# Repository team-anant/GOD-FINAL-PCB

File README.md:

# GOD FINAL PCB
IDEAS
FAILSAFE POWER SUPPLY FOR EPS AND BEACON LIKE DIRECT PANEL TO EPS WITHOUT BUCK AND SHIT JUST PLAIN POWER 
GOALS
1. POWER SUPPLY
	A)PANEL IN 
		ARCHITECTURE AND CONFIG OF THE PANELS
		
2. POWER STORAGE
	BATTERY CONFIG: 2S2P
	BATTERY HEATER?
	BATTERY MONITORING?
	
3. POWER MONITORING
	PGEN MONITORING
	PNET UTIL MONITORING
4. POWER BUS WITH DEDICATED MONITORED LINES
	OBC
	PAYLOAD 1
	PAYLOAD 2
	PAYLOAD 3
	TTC 
	ADCS SENSOR PACKAGE
	ADCS CONTROL PACKAGE
	
5. OCPC DEDICATED LINES
	OBC
	PAYLOAD 1
	PAYLOAD 2
	PAYLOAD 3
	TTC 
	ADCS SENSOR PACKAGE
	ADCS CONTROL PACKAGE
6. POWER MONITORING INTERFACE
7. SENSOR INTERFACE
	BNO055
	GPS
	BEAGLE BONE BLACK
	
8. DATA STORAGE
9. DATA PACKETIZATION
10. DATA BEACON
11. WATCHDOG
	AUTO WATCHDOG
12. TEMPEARTURE MONITORING SYSTEM
	LTC2896

FAILOVER MODES:-
1. EPS OCPS

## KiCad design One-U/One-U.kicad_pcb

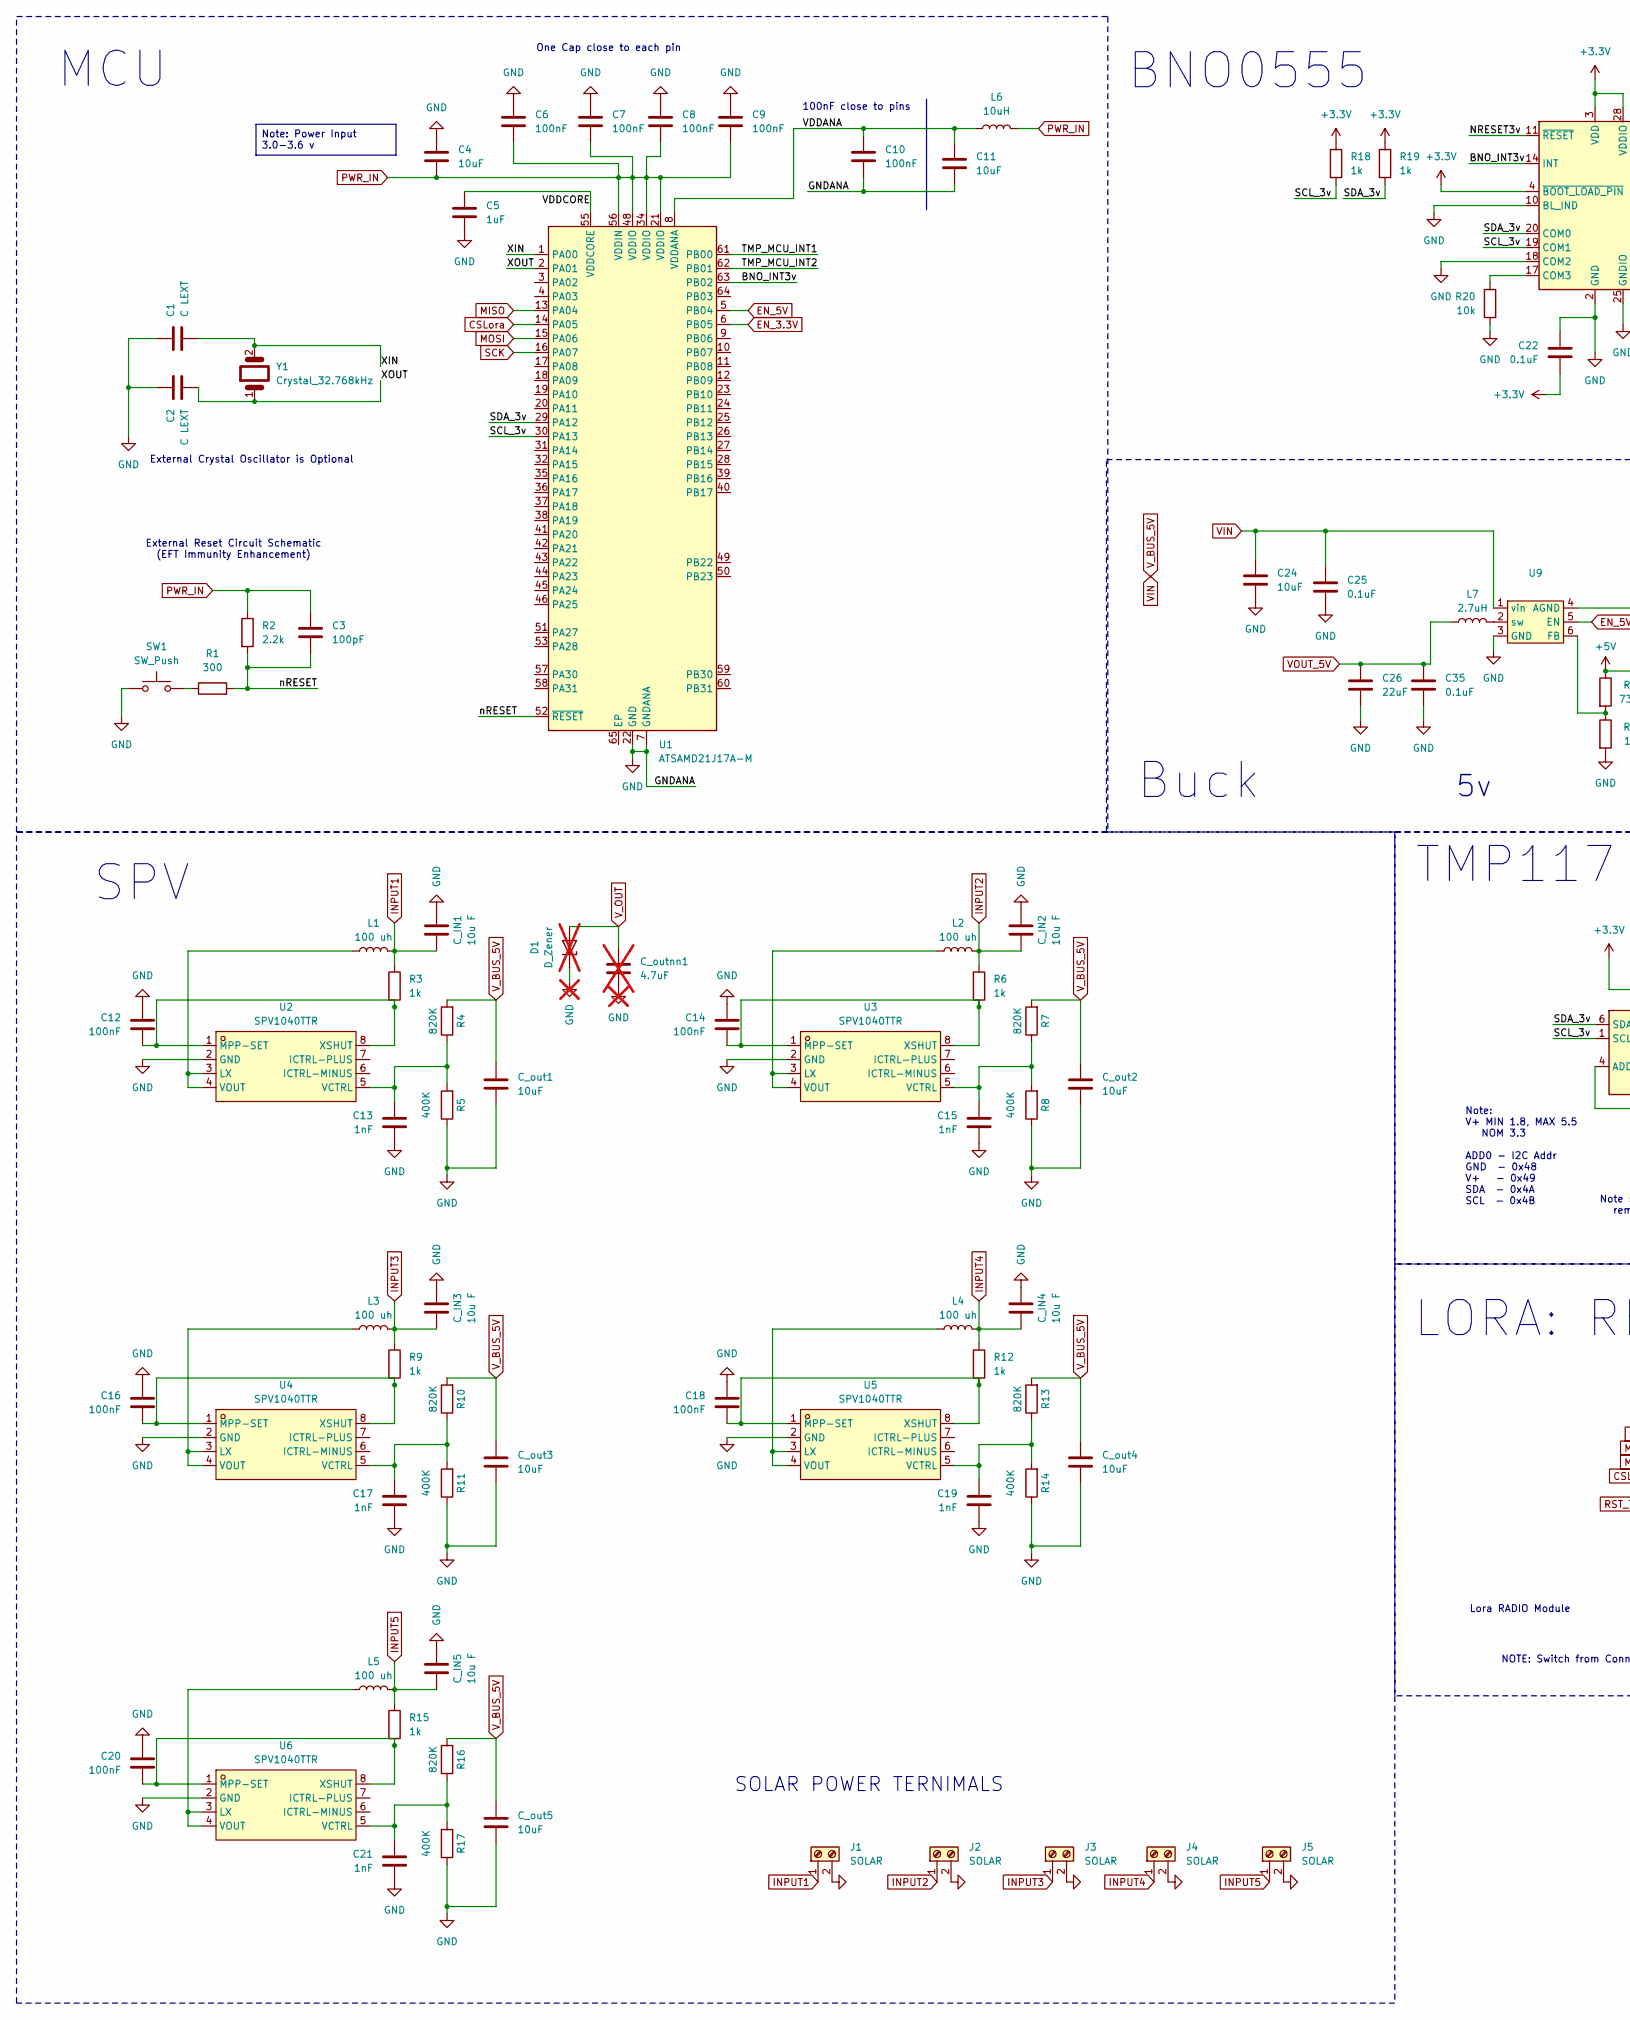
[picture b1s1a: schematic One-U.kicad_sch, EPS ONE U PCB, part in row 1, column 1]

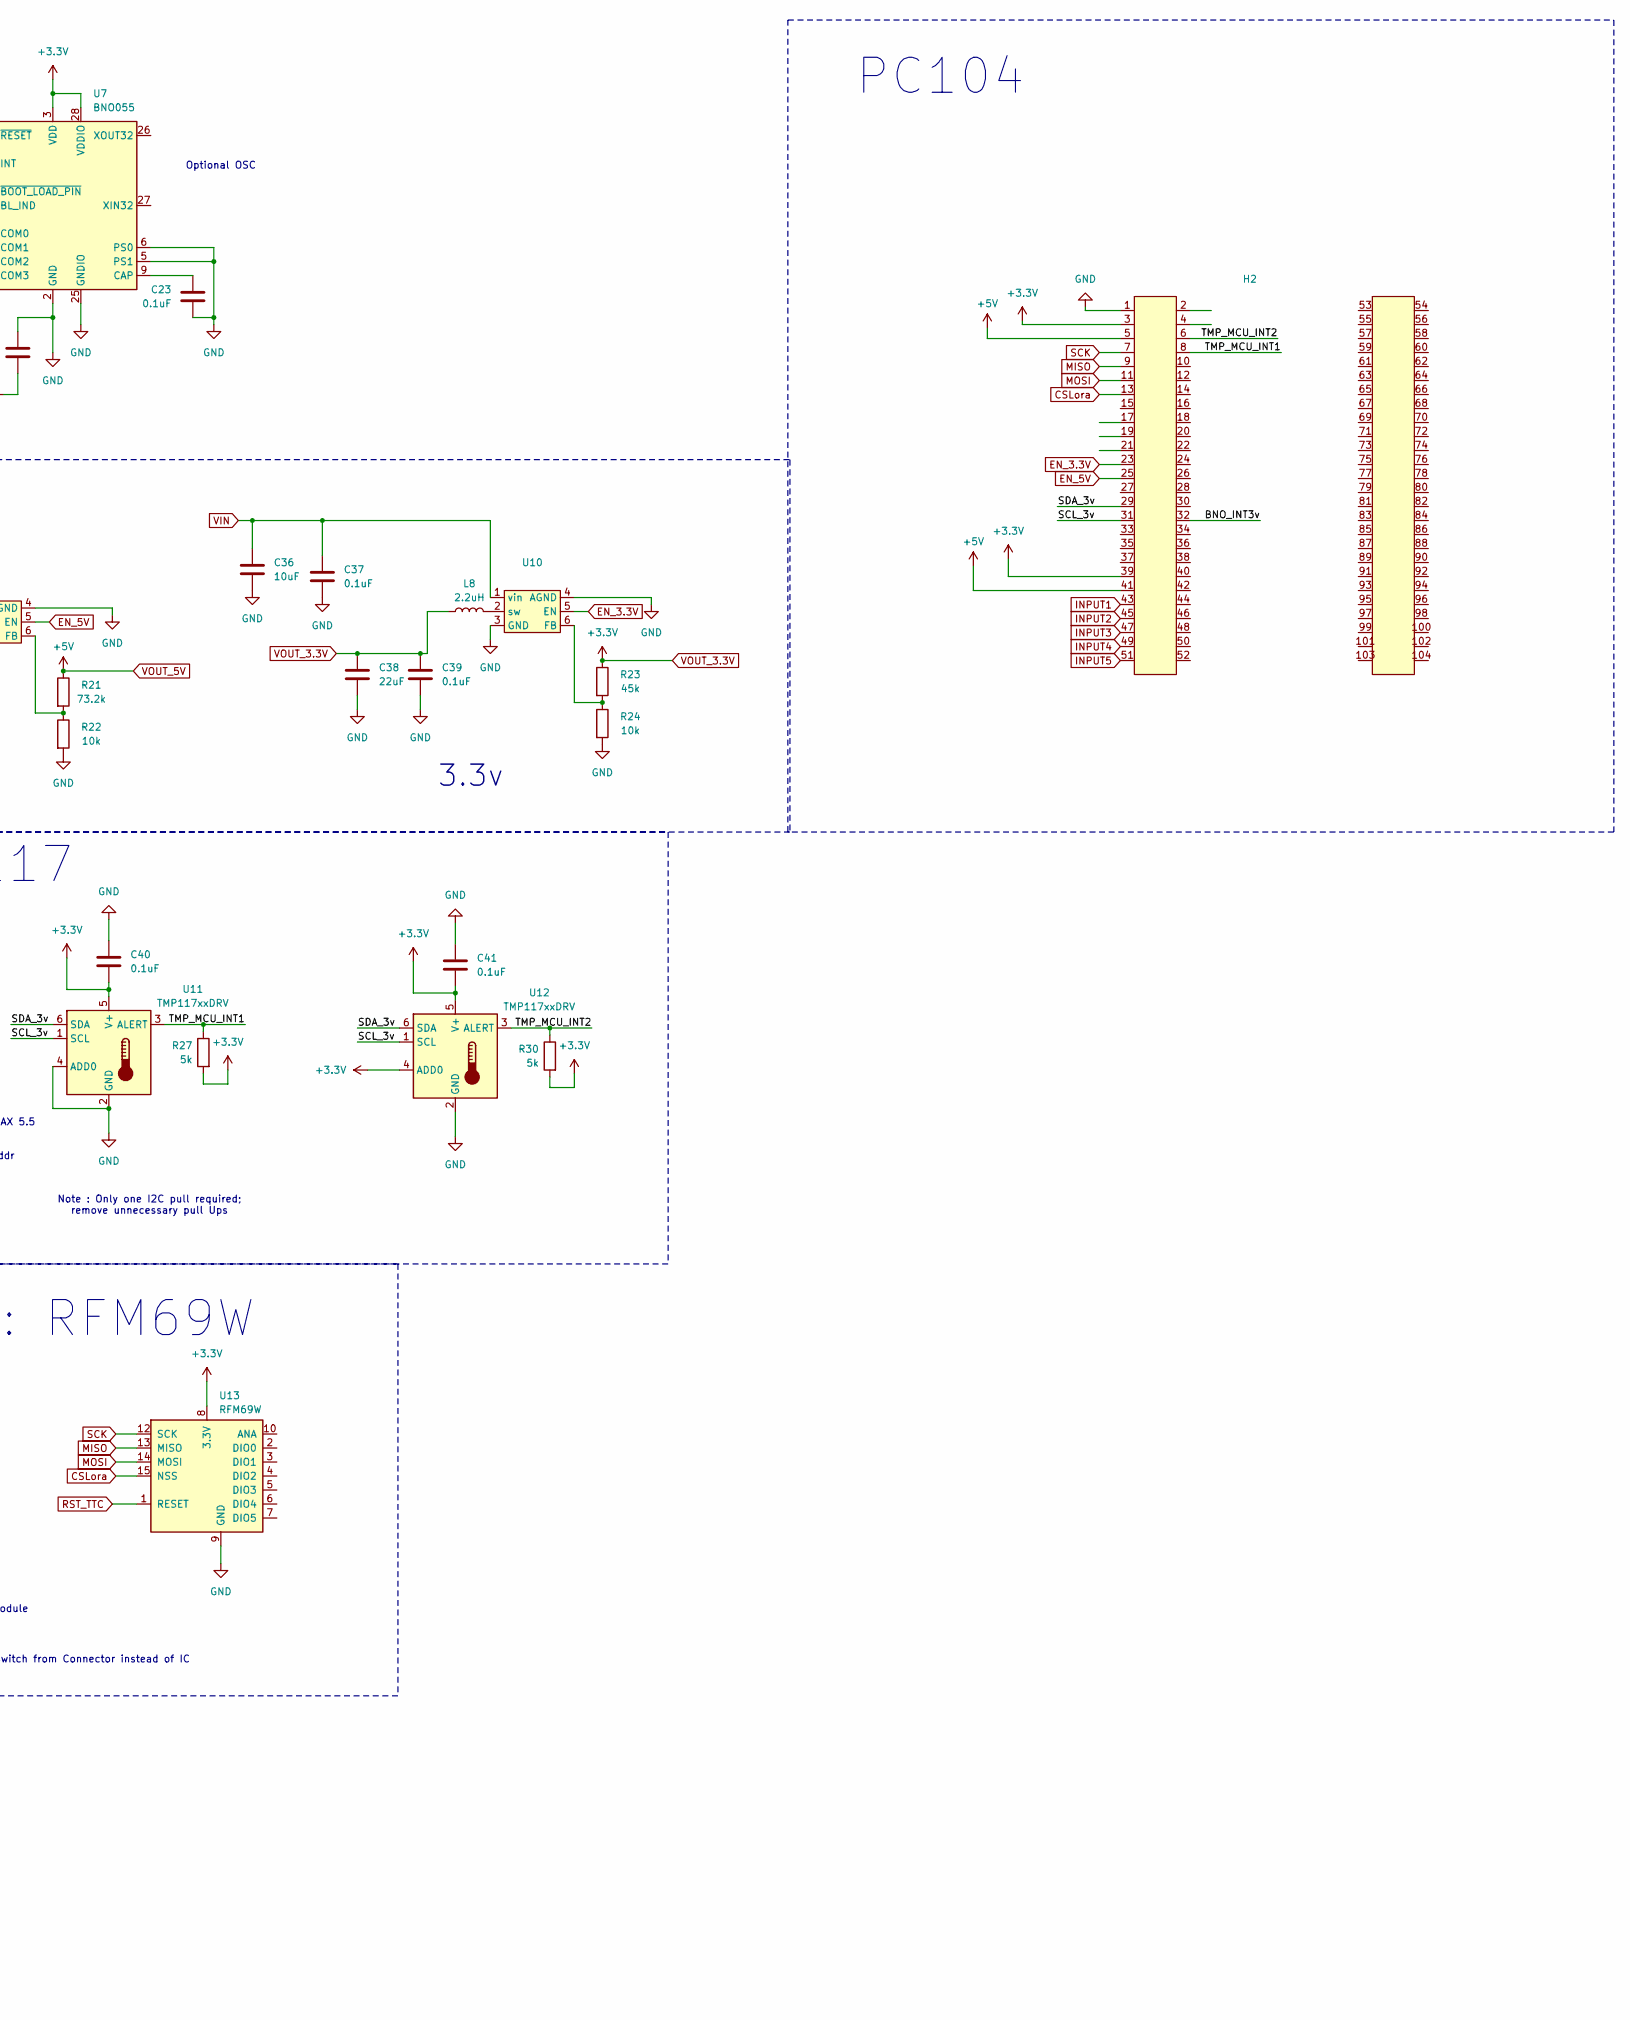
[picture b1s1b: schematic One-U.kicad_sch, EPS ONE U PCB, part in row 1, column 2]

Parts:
C1, C2: C LEXT; C_0603_1608Metric
C3: 100pF; C_0603_1608Metric
C4, C11, C24, C36: 10uF; C_0603_1608Metric
C5: 1uF; C_0603_1608Metric
C6, C7, C8, C9, C10, C12, C14, C16, C18, C20: 100nF; C_0603_1608Metric
C13, C15, C17, C19, C21: 1nF; C_0603_1608Metric
C22, C23, C25, C35, C37, C39, C40, C41: 0.1uF; C_0603_1608Metric
C26, C38: 22uF; C_0603_1608Metric
C_IN1, C_IN2, C_IN3, C_IN4, C_IN5: 10u F; C_0603_1608Metric
C_out1, C_out2, C_out3, C_out4, C_out5: 10uF; C_0603_1608Metric
C_outnn1: 4.7uF; C_0603_1608Metric; not fitted
D1: D_Zener; D_1210_3225Metric; not fitted
H2: PC104-Standard
J1, J2, J3, J4, J5: SOLAR; TerminalBlock_Phoenix_PT-1,5-2-5.0-H_1x02_P5.00mm_Horizontal
L1, L2, L3, L4, L5: 100 uh; L_Coilcraft_XAL6060-XXX
L6: 10uH; L_0805_2012Metric
L7: 2.7uH; L_Wuerth_MAPI-4020
L8: 2.2uH; L_Wuerth_MAPI-4020
R1: 300; R_0603_1608Metric
R2: 2.2k; R_0603_1608Metric
R3, R6, R9, R12, R15, R18, R19: 1k; R_0603_1608Metric
R4, R7, R10, R13, R16: 820K; R_0603_1608Metric
R5, R8, R11, R14, R17: 400K; R_0603_1608Metric
R20, R22, R24: 10k; R_0603_1608Metric
R21: 73.2k; R_0603_1608Metric
R23: 45k; R_0603_1608Metric
R27, R30: 5k; R_0603_1608Metric
SW1: SW_Push; SW_Push_1P1T_NO_E-Switch_TL3301NxxxxxG
U1: ATSAMD21J17A-M; QFN-64-1EP_9x9mm_P0.5mm_EP4.7x4.7mm
U2, U3, U4, U5, U6: SPV1040TTR; TSSOP-8_L4.4-W3.0-P0.65-LS6.4-BL; LCSC Part C221500
U7: BNO055; LGA-28_5.2x3.8mm_P0.5mm
U9, U10: SOT-23-6_Handsoldering
U11, U12: TMP117xxDRV; WSON-6-1EP_2x2mm_P0.65mm_EP1x1.6mm
U13: RFM69W; HOPERF_RFM69HW
Y1: Crystal_32.768kHz; Crystal_AT310_D3.0mm_L10.0mm_Vertical

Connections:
/BNO_INT3v: H2.32, U1.63 (PB02), U7.14 (INT)
/NRESET3v: U7.11 (~RESET)
/SCL_3v: H2.31, R18.2, U1.30 (PA13), U7.19 (COM1), U11.1 (SCL), U12.1 (SCL); also elsewhere on the board
/SDA_3v: H2.29, R19.2, U1.29 (PA12), U7.20 (COM0), U11.6 (SDA), U12.6 (SDA); also elsewhere on the board
/TMP_MCU_INT1: H2.8, R27.1, U1.61 (PB00), U11.3 (ALERT)
/TMP_MCU_INT2: H2.6, R30.1, U1.62 (PB01), U12.3 (ALERT)
/VDDANA: C10.1, C11.1, L6.1, U1.8 (VDDANA)
/VDDCORE: C5.1, U1.55 (VDDCORE)
/XIN: C1.2, U1.1 (PA00), Y1.2
/XOUT: C2.2, U1.2 (PA01), Y1.1
/nRESET: C3.2, R1.2, R2.2, U1.52 (~RESET)
CSLora: H2.13, U1.14 (PA05), U13.15 (NSS)
EN_3.3V: H2.23, U1.6 (PB05), U10.5 (EN)
EN_5V: H2.25, U1.5 (PB04), U9.5 (EN)
GND: C1.1, C2.1, C4.1, C5.2, C6.1, C7.1, C8.1, C9.1, C10.2, C11.2, C12.1, C13.2, C14.1, C15.2, C16.1, C17.2, C18.1, C19.2, C20.1, C21.2, C22.1, C23.2, C24.2, C25.2, C26.2, C35.2, C36.2, C37.2, C38.2, C39.2, C40.1, C41.1, C_IN1.2, C_IN2.2, C_IN3.2, C_IN4.2, C_IN5.2, C_out1.2, C_out2.2, C_out3.2, C_out4.2, C_out5.2, H2.1, J1.2, J2.2, J3.2, J4.2, J5.2, R5.1, R8.1, R11.1, R14.1, R17.1, R20.2, R22.2, R24.2, SW1.1, U1.7 (GNDANA), U1.22 (GND), U1.33 (GND), U1.47 (GND), U1.54 (GND), U2.2 (GND), U3.2 (GND), U4.2 (GND), U5.2 (GND), U6.2 (GND), U7.2 (GND), U7.5 (PS1), U7.6 (PS0), U7.10 (BL_IND), U7.18 (COM2), U7.25 (GNDIO), U9.3 (GND), U9.4 (AGND), U10.3 (GND), U10.4 (AGND), U11.2 (GND), U11.4 (ADD0), U12.2 (GND), U13.9 (GND), U13.11 (GND); also elsewhere on the board
INPUT1: C_IN1.1, H2.43, J1.1, L1.2, R3.1
INPUT2: C_IN2.1, H2.45, J2.1, L2.2, R6.1
INPUT3: C_IN3.1, H2.47, J3.1, L3.2, R9.1
INPUT4: C_IN4.1, H2.49, J4.1, L4.2, R12.1
INPUT5: C_IN5.1, H2.51, J5.1, L5.2, R15.1
MISO: H2.9, U1.13 (PA04), U13.13 (MISO)
MOSI: H2.11, U1.15 (PA06), U13.14 (MOSI)
unnamed: C_outnn1.2, D1.2 (A)
unnamed 26: U13.10 (ANA); also elsewhere on the board
unnamed: R1.1, SW1.2
unnamed: L1.1, U2.3 (LX), U2.4 (VOUT)
unnamed: C12.2, R3.2, U2.1 (MPP-SET), U2.8 (XSHUT)
unnamed: C13.1, R4.1, R5.2, U2.5 (VCTRL)
unnamed: L2.1, U3.3 (LX), U3.4 (VOUT)
unnamed: C14.2, R6.2, U3.1 (MPP-SET), U3.8 (XSHUT)
unnamed: C15.1, R7.1, R8.2, U3.5 (VCTRL)
unnamed: L3.1, U4.3 (LX), U4.4 (VOUT)
unnamed: C16.2, R9.2, U4.1 (MPP-SET), U4.8 (XSHUT)
unnamed: C17.1, R10.1, R11.2, U4.5 (VCTRL)
unnamed: L4.1, U5.3 (LX), U5.4 (VOUT)
unnamed: C18.2, R12.2, U5.1 (MPP-SET), U5.8 (XSHUT)
unnamed: C19.1, R13.1, R14.2, U5.5 (VCTRL)
unnamed: L5.1, U6.3 (LX), U6.4 (VOUT)
unnamed: C20.2, R15.2, U6.1 (MPP-SET), U6.8 (XSHUT)
unnamed: C21.1, R16.1, R17.2, U6.5 (VCTRL)
unnamed: C23.1, U7.9 (CAP)
unnamed: R20.1, U7.17 (COM3)
unnamed: R21.2, R22.1, U9.6 (FB)
unnamed: L7.1, U9.2 (sw)
unnamed: R23.2, R24.1, U10.6 (FB)
unnamed: L8.1, U10.2 (sw)
PWR_IN: C3.1, C4.2, C6.2, C7.2, C8.2, C9.2, L6.2, R2.1, U1.21 (VDDIO), U1.34 (VDDIO), U1.48 (VDDIO), U1.56 (VDDIN)
RST_TTC: U1.10 (PB07), U13.1 (RESET)
SCK: H2.7, U1.16 (PA07), U13.12 (SCK)
STAT: U1.9 (PB06); also elsewhere on the board
VIN: C24.1, C25.1, C36.1, C37.1, C_out1.1, C_out2.1, C_out3.1, C_out4.1, C_out5.1, R4.2, R7.2, R10.2, R13.2, R16.2, U9.1 (vin), U10.1 (vin); also elsewhere on the board
VOUT_3.3V: C22.2, C38.1, C39.1, C40.2, C41.2, H2.3, H2.39, L8.2, R18.1, R19.1, R23.1, R27.2, R30.2, U7.3 (VDD), U7.4 (~BOOT_LOAD_PIN), U7.28 (VDDIO), U11.5 (V+), U12.4 (ADD0), U12.5 (V+), U13.8 (3.3V)
VOUT_5V: C26.1, C35.1, H2.5, H2.41, L7.2, R21.1

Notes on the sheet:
Optional OSC
100nF close to pins
Buck
Note: V+ MIN 1.8, MAX 5.5 NOM 3.3 ADD0 - I2C Addr GND - 0x48 V+ - 0x49 SDA - 0x4A SCL - 0x4B
One Cap close to each pin
MCU
External Reset Circuit Schematic (EFT Immunity Enhancement)
Lora RADIO Module
SPV
PC104
NOTE: Switch from Connector instead of IC
SOLAR POWER TERNIMALS
TMP117
Note : Only one I2C pull required; remove unnecessary pull Ups
LORA: RFM69W
3.3v
External Crystal Oscillator is Optional
BNO0555
Note: Power Input 3.0-3.6 v

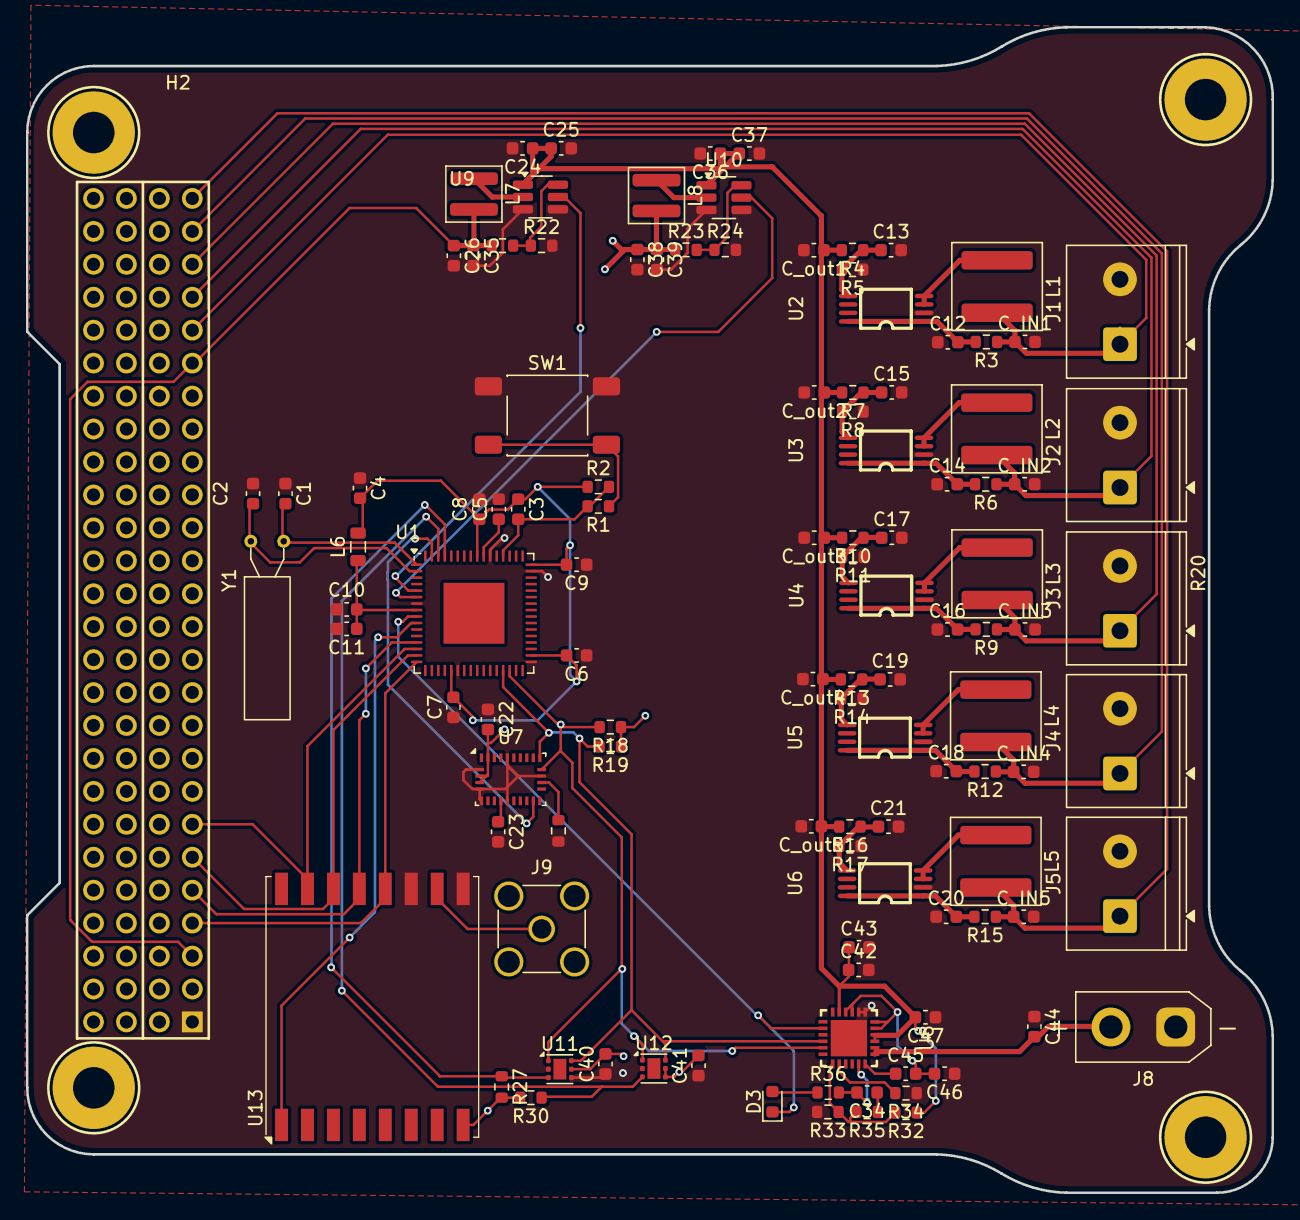
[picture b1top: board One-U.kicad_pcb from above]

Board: 4 copper layers, 96.0 x 89.9 mm, 113 parts (0 on the bottom side), 59 nets.

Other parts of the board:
C34: 4.7uF; C_0603_1608Metric
C42, C43: 22uF; C_0603_1608Metric
C44, C46: 10uF; C_0603_1608Metric
C45: 47uF; C_0603_1608Metric
C47: 1uF; C_0603_1608Metric
D3: LED; LED_0603_1608Metric
J8: Conn_01x02_Socket; AMASS_XT30UPB-F_1x02_P5.0mm_Vertical
J9: Conn_Coaxial_Small; SMA_Amphenol_132134-11_Vertical
R32: 5.23k; R_0603_1608Metric
R33: 30.1k; R_0603_1608Metric
R34: 3.16k; R_0603_1608Metric
R35, R36: 10k; R_0603_1608Metric
U8: BQ25883RGER; VFQFPN-24_L4.0-W4.0-P0.50-BL-EP2.8

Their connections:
/SCL_3v: U8.5 (SCL); also elsewhere on the board
/SDA_3v: U8.4 (SDA); also elsewhere on the board
GND: C42.2, C43.2, C44.1, C46.1, C47.1, J8.1, R33.2, R34.1, U8.19 (GND), U8.20 (GND), U8.25 (EP); also elsewhere on the board
unnamed: C34.1, R35.1
unnamed: C45.2, C46.2, U8.17 (SW), U8.18 (SW), U8.21 (PMID), U8.22 (PMID)
unnamed: D3.2 (A), R36.1
unnamed 26: J9.1 (In); also elsewhere on the board
unnamed: C45.1, U8.12 (BTST)
unnamed: R34.2, U8.8 (ILIM)
unnamed: C34.2, R36.2, U8.11 (REGN)
STAT: D3.1 (K), U8.2 (STAT); also elsewhere on the board
THM: R32.2, R33.1, R35.2, U8.7 (TS)
VIN: C42.1, C43.1, C47.2, R32.1, U8.15 (SYS), U8.16 (SYS), U8.23 (VBUS); also elsewhere on the board
V_BAT: C44.2, J8.2, U8.13 (BAT), U8.14 (BAT)

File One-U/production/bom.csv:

Designator,Footprint,Quantity,Value,LCSC Part #
"C1, C2",0603,2,C LEXT,
"C10, C12, C14, C16, C18, C20, C6, C7, C8, C9",0603,10,100nF,
"C11, C24, C36, C4, C44, C46, C_OUT1, C_OUT2, C_OUT3, C_OUT4, C_OUT5",0603,11,10uF,
"C13, C15, C17, C19, C21",0603,5,1nF,
"C22, C23, C25, C35, C37, C39, C40, C41",0603,8,0.1uF,
"C26, C38, C42, C43",0603,4,22uF,
C3,0603,1,100pF,
C34,0603,1,4.7uF,
C45,0603,1,47uF,
"C47, C5",0603,2,1uF,
"C_IN1, C_IN2, C_IN3, C_IN4, C_IN5",0603,5,10u F,
D3,0603,1,LED,
H2,PC104-Standard,1,~,
"J1, J2, J3, J4, J5","TerminalBlock_Phoenix_PT-1,5-2-5.0-H_1x02_P5.00mm_Horizontal",5,SOLAR,
J8,AMASS_XT30UPB-F_1x02_P5.0mm_Vertical,1,Conn_01x02_Socket,
J9,SMA_Amphenol_132134-11_Vertical,1,Conn_Coaxial_Small,
"L1, L2, L3, L4, L5",L_Coilcraft_XAL6060-XXX,5,100 uh,
L6,0805,1,10uH,
L7,L_Wuerth_MAPI-4020,1,2.7uH,
L8,L_Wuerth_MAPI-4020,1,2.2uH,
R1,0603,1,300,
"R10, R13, R16, R4, R7",0603,5,820K,
"R11, R14, R17, R5, R8",0603,5,400K,
"R12, R15, R18, R19, R3, R6, R9",0603,7,1k,
R2,0603,1,2.2k,
"R20, R22, R24, R35, R36",0603,5,10k,
R21,0603,1,73.2k,
R23,0603,1,45k,
"R27, R30",0603,2,5k,
R32,0603,1,5.23k,
R33,0603,1,30.1k,
R34,0603,1,3.16k,
SW1,SW_Push_1P1T_NO_E-Switch_TL3301NxxxxxG,1,SW_Push,
U1,QFN-64-1EP_9x9mm_P0.5mm_EP4.7x4.7mm,1,ATSAMD21J17A-M,
"U10, U9",SOT-23-6_Handsoldering,2,~,
"U11, U12",WSON-6-1EP_2x2mm_P0.65mm_EP1x1.6mm,2,TMP117xxDRV,
U13,HOPERF_RFM69HW,1,RFM69W,
"U2, U3, U4, U5, U6",TSSOP-8_L4.4-W3.0-P0.65-LS6.4-BL,5,SPV1040TTR,C221500
U7,LGA-28_5.2x3.8mm_P0.5mm,1,BNO055,
U8,VFQFPN-24_L4.0-W4.0-P0.50-BL-EP2.8,1,BQ25883RGER,C544362
Y1,Crystal_AT310_D3.0mm_L10.0mm_Horizontal,1,Crystal_32.768kHz,

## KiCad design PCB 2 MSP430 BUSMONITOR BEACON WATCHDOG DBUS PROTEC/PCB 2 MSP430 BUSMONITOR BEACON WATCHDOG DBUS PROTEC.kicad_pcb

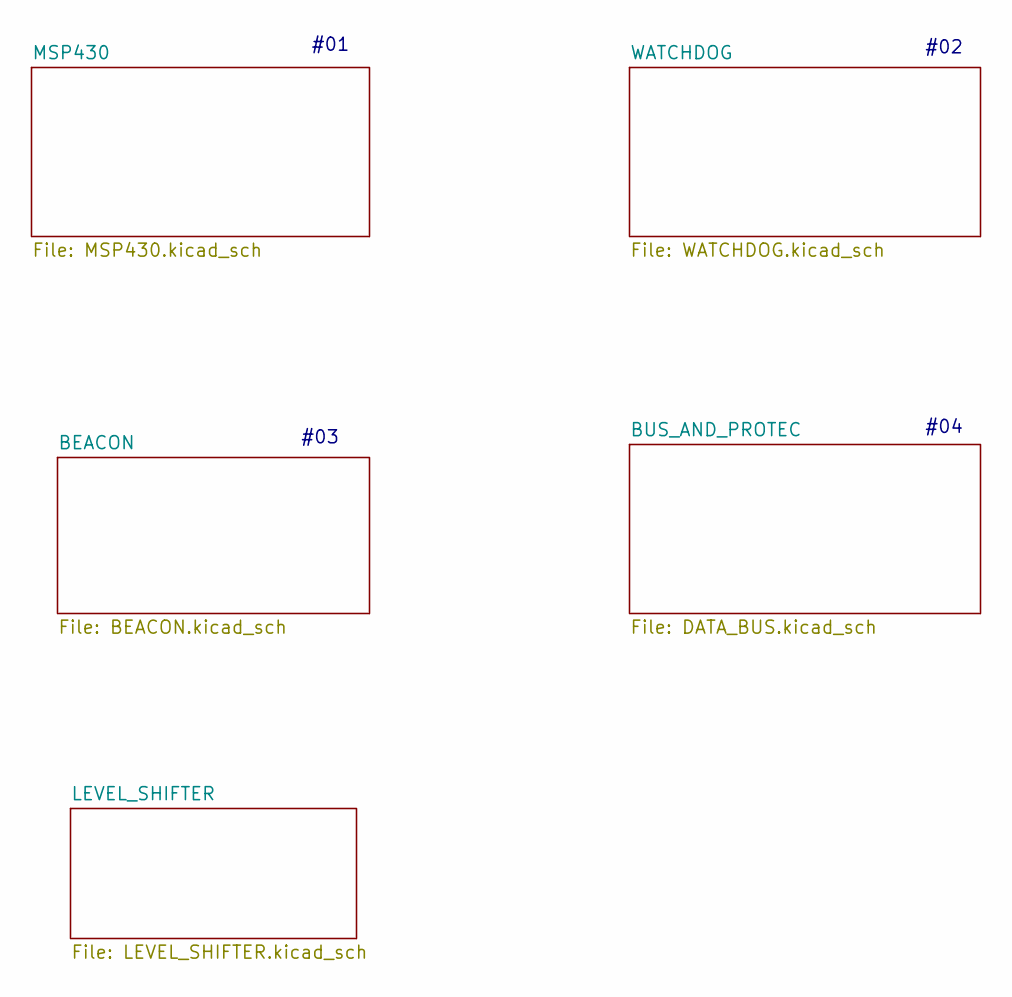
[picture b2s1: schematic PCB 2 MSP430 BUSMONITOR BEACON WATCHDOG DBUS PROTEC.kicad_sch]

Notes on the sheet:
#03
#01
#04
#02

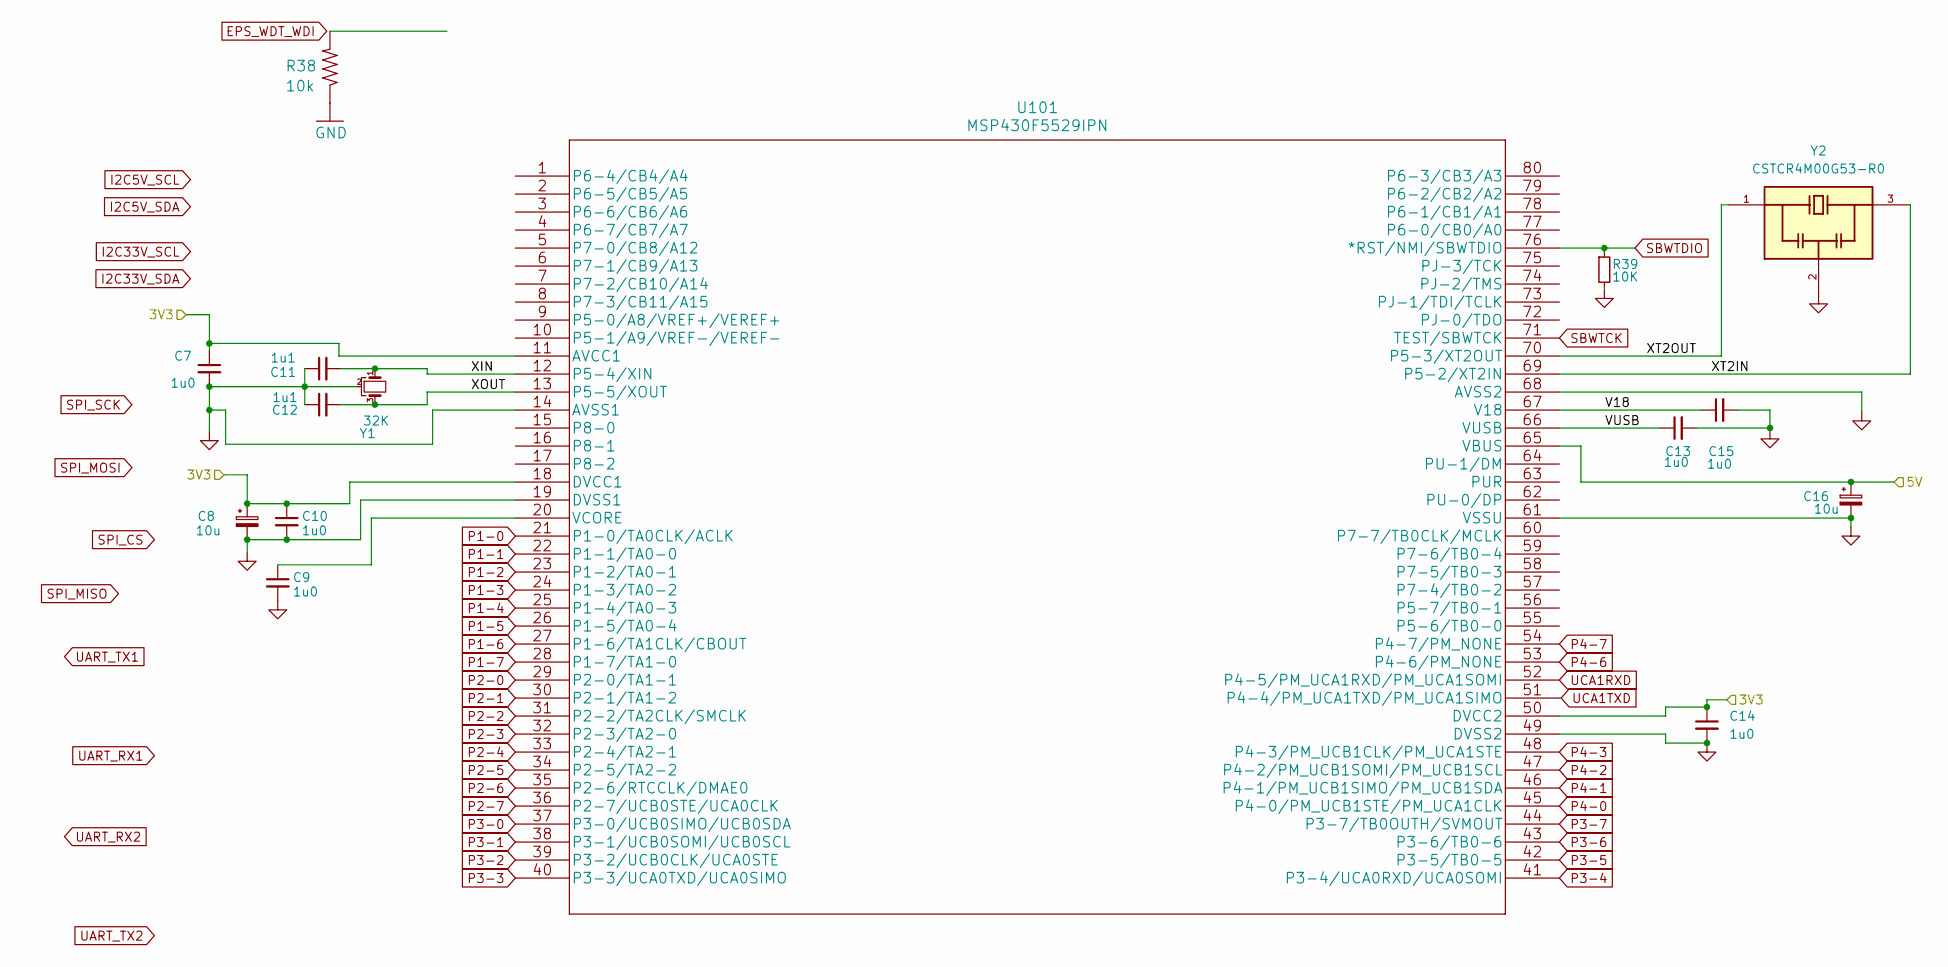
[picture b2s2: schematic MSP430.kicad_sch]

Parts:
C7, C9, C10, C14: 1u0; C_0603_1608Metric
C8: 10u; CP_Elec_3x5.3
C11, C12: 1u1; C_0603_1608Metric
C13, C15: 1u0; C_0402_1005Metric_Pad0.74x0.62mm_HandSolder
C16: 10u; CP_Elec_4x3.9
R38: 10k; R_0603_1608Metric
R39: 10K; R_0603_1608Metric
U101: MSP430F5529IPN
Y1: 32K; Crystal_AT310_D3.0mm_L10.0mm_Horizontal_1EP_style1
Y2: CSTCR4M00G53-R0; OSC_CSTCR4M00G53-R0; PARTREV JGC42-8797

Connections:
/MSP430/3V3: C7.1, C8.1, C10.1, C14.1, U101.11 (AVCC1), U101.18 (DVCC1), U101.50 (DVCC2)
/MSP430/5V: C16.1, U101.65 (VBUS)
/MSP430/V18: C15.1, U101.67 (V18)
/MSP430/VUSB: C13.1, U101.66 (VUSB)
/MSP430/XIN: C11.2, U101.12 (P5-4/XIN), Y1.1
/MSP430/XOUT: C12.2, U101.13 (P5-5/XOUT), Y1.3
GND: C7.2, C8.2, C9.2, C10.2, C11.1, C12.1, C13.2, C14.2, C15.2, C16.2, R38.1, R39.2, U101.14 (AVSS1), U101.19 (DVSS1), U101.49 (DVSS2), U101.61 (VSSU), U101.68 (AVSS2), Y1.2, Y2.2; also elsewhere on the board
unnamed: U101.69 (P5-2/XT2IN), Y2.3
unnamed: U101.70 (P5-3/XT2OUT), Y2.1
unnamed: C9.1, U101.20 (VCORE)
SBWTDIO: R39.1, U101.76 (*RST/NMI/SBWTDIO)

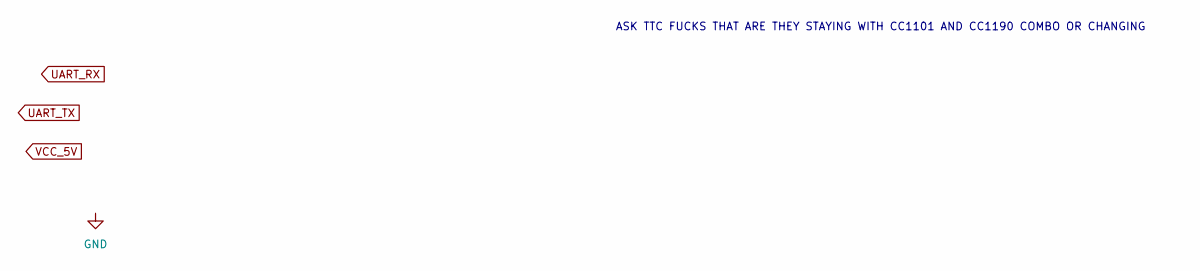
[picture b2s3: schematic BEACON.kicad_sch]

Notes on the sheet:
ASK TTC FUCKS THAT ARE THEY STAYING WITH CC1101 AND CC1190 COMBO OR CHANGING

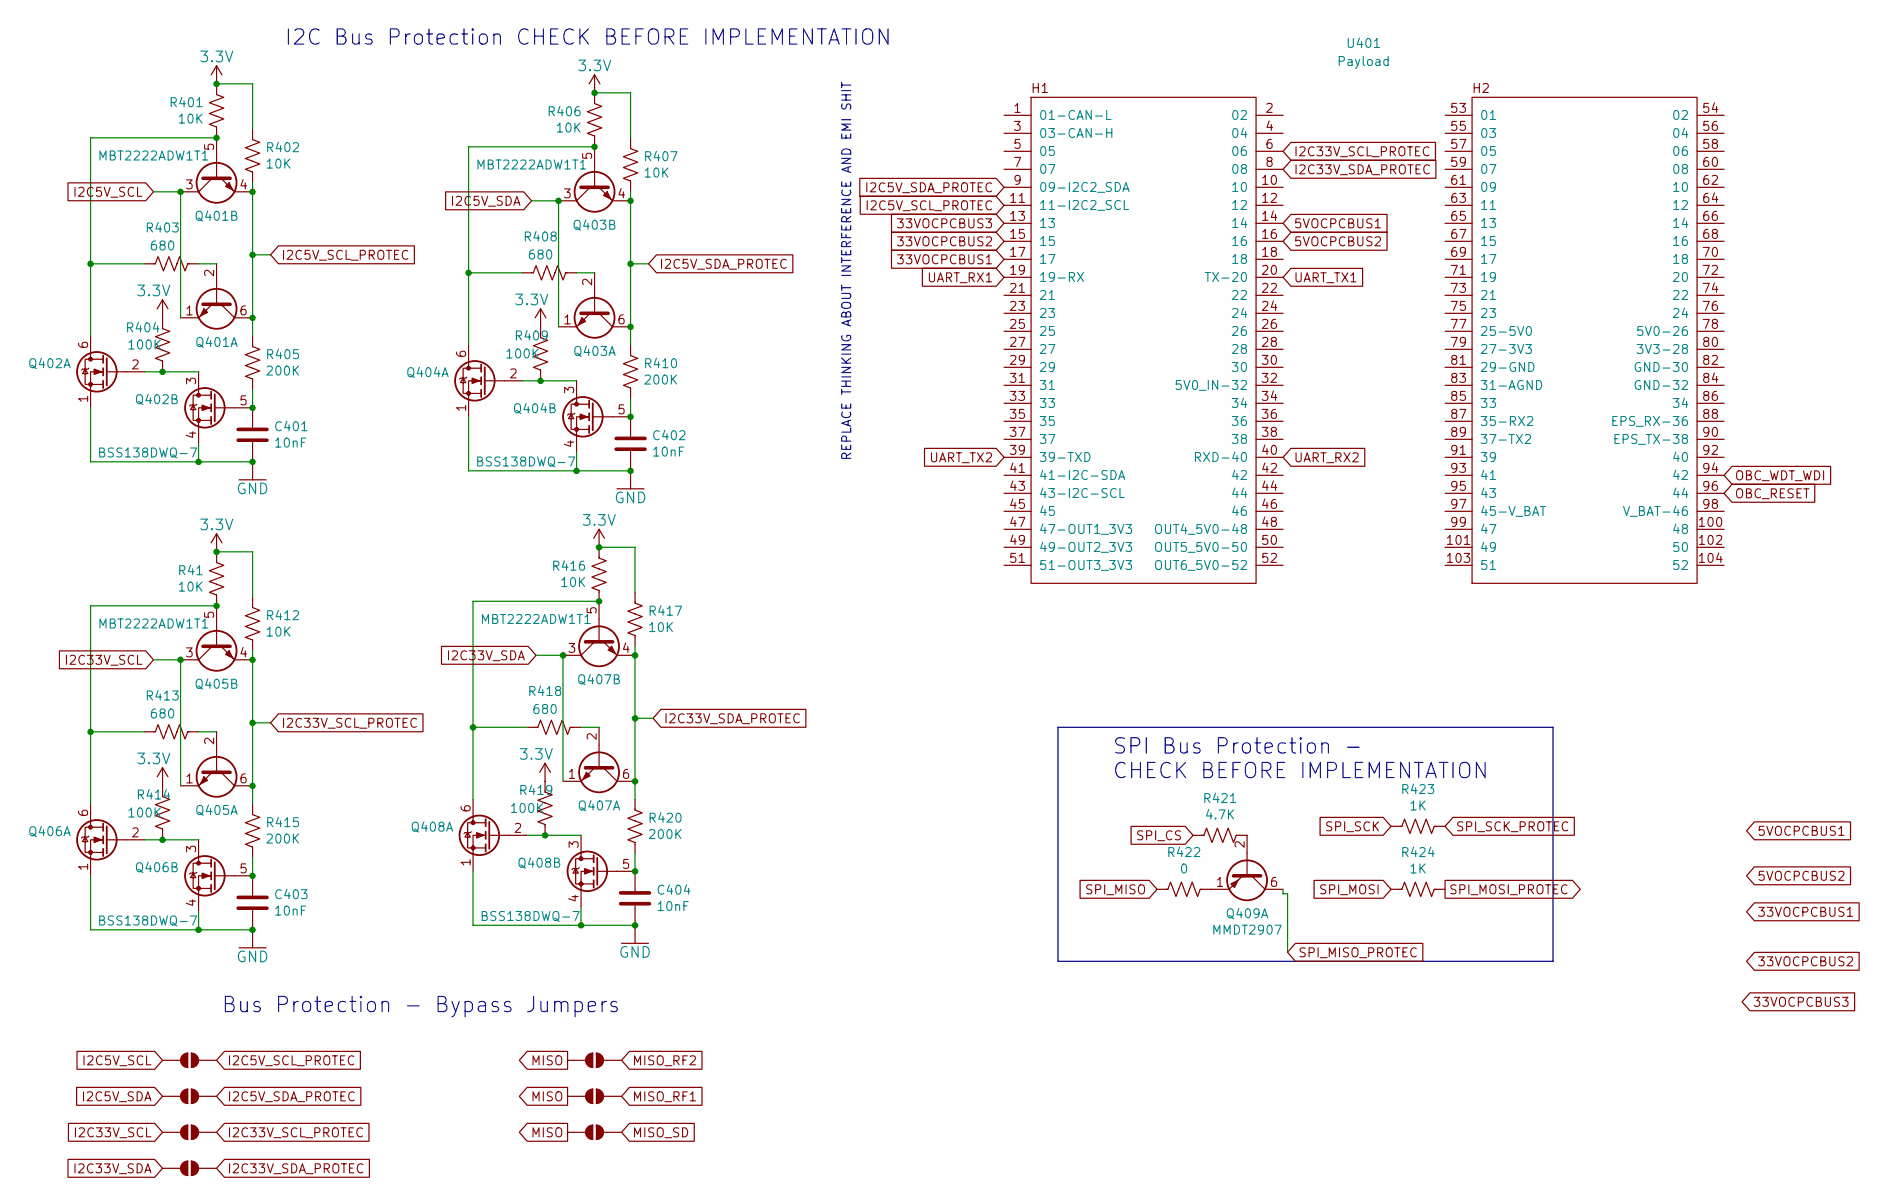
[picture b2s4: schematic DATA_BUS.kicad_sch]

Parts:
C401, C402, C403, C404: 10nF; C_0603_1608Metric
JP401, JP402, JP403, JP404, JP405, JP406, JP407: SolderJumper_2_Open; SolderJumper-2_P1.3mm_Open_RoundedPad1.0x1.5mm
Q401, Q403, Q405, Q407: MBT2222ADW1T1; SOT-363_SC-70-6; Manufacturer_Part_Number MBT2222ADW1T1G
Q402, Q404, Q406, Q408: BSS138DWQ-7; SOT-363_SC-70-6_Handsoldering; Manufacturer_Part_Number BSS138DWQ-7
Q409: MMDT2907; SOT-363_SC-70-6; Manufacturer_Part_Number MMDT2907AQ-7-F
R41, R401, R402, R406, R407, R412, R416, R417: 10K; R_0603_1608Metric
R403, R408, R413, R418: 680; R_0603_1608Metric
R404, R409, R414, R419: 100K; R_0603_1608Metric
R405, R410, R415, R420: 200K; R_0603_1608Metric
R421: 4.7K; R_0603_1608Metric
R422: 0; R_0603_1608Metric
R423, R424: 1K; R_0603_1608Metric
U401: Payload; PC104-Standard; JLCPCB Part# ESQ-126-24-G-D

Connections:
3.3V: R41.1, R401.1, R402.1, R404.1, R406.1, R407.1, R409.1, R412.1, R414.1, R416.1, R417.1, R419.1; also elsewhere on the board
5VOCPCBUS1: U401.14
5VOCPCBUS2: U401.16
33VOCPCBUS1: U401.17
33VOCPCBUS2: U401.15
33VOCPCBUS3: U401.13
GND: C401.2, C402.2, C403.2, C404.2, Q402.1 (S2), Q402.4 (S1), Q404.1 (S2), Q404.4 (S1), Q406.1 (S2), Q406.4 (S1), Q408.1 (S2), Q408.4 (S1); also elsewhere on the board
I2C5V_SCL: JP401.1 (A), Q401.1 (E1), Q401.3 (C2)
I2C5V_SCL_PROTEC: JP401.2 (B), Q401.4 (E2), Q401.6 (C1), R402.2, R405.1, U401.11 (11-I2C2_SCL)
I2C5V_SDA: JP402.1 (A), Q403.1 (E1), Q403.3 (C2)
I2C5V_SDA_PROTEC: JP402.2 (B), Q403.4 (E2), Q403.6 (C1), R407.2, R410.1, U401.9 (09-I2C2_SDA)
I2C33V_SCL: JP403.1 (A), Q405.1 (E1), Q405.3 (C2)
I2C33V_SCL_PROTEC: JP403.2 (B), Q405.4 (E2), Q405.6 (C1), R412.2, R415.1, U401.6
I2C33V_SDA: JP404.1 (A), Q407.1 (E1), Q407.3 (C2)
I2C33V_SDA_PROTEC: JP404.2 (B), Q407.4 (E2), Q407.6 (C1), R417.2, R420.1, U401.8
MISO: JP405.1 (A), JP406.1 (A), JP407.1 (A)
MISO_RF1: JP406.2 (B)
MISO_RF2: JP405.2 (B)
MISO_SD: JP407.2 (B)
unnamed: Q401.2 (B1), R403.1
unnamed: Q401.5 (B2), Q402.6 (D1), R401.2, R403.2
unnamed: Q402.2 (G2), Q402.3 (D2), R404.2
unnamed: C401.1, Q402.5 (G1), R405.2
unnamed: Q403.2 (B1), R408.1
unnamed: Q403.5 (B2), Q404.6 (D1), R406.2, R408.2
unnamed: Q404.2 (G2), Q404.3 (D2), R409.2
unnamed: C402.1, Q404.5 (G1), R410.2
unnamed: Q405.2 (B1), R413.1
unnamed: Q405.5 (B2), Q406.6 (D1), R41.2, R413.2
unnamed: Q406.2 (G2), Q406.3 (D2), R414.2
unnamed: C403.1, Q406.5 (G1), R415.2
unnamed: Q407.2 (B1), R418.1
unnamed: Q407.5 (B2), Q408.6 (D1), R416.2, R418.2
unnamed: Q408.2 (G2), Q408.3 (D2), R419.2
unnamed: C404.1, Q408.5 (G1), R420.2
unnamed: Q409.2 (B1), R421.1
unnamed: Q409.1 (E1), R422.1
OBC_RESET: U401.96 (44); also elsewhere on the board
OBC_WDT_WDI: U401.94 (42); also elsewhere on the board
SPI_CS: R421.2
SPI_MISO: R422.2
SPI_MISO_PROTEC: Q409.6 (C1)
SPI_MOSI: R424.1
SPI_MOSI_PROTEC: R424.2
SPI_SCK: R423.2
SPI_SCK_PROTEC: R423.1
UART_RX1: U401.19 (19-RX)
UART_RX2: U401.40 (RXD-40)
UART_TX1: U401.20 (TX-20)
UART_TX2: U401.39 (39-TXD)

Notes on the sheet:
Bus Protection - Bypass Jumpers
I2C Bus Protection CHECK BEFORE IMPLEMENTATION
SPI Bus Protection - CHECK BEFORE IMPLEMENTATION
REPLACE THINKING ABOUT INTERFERENCE AND EMI SHIT

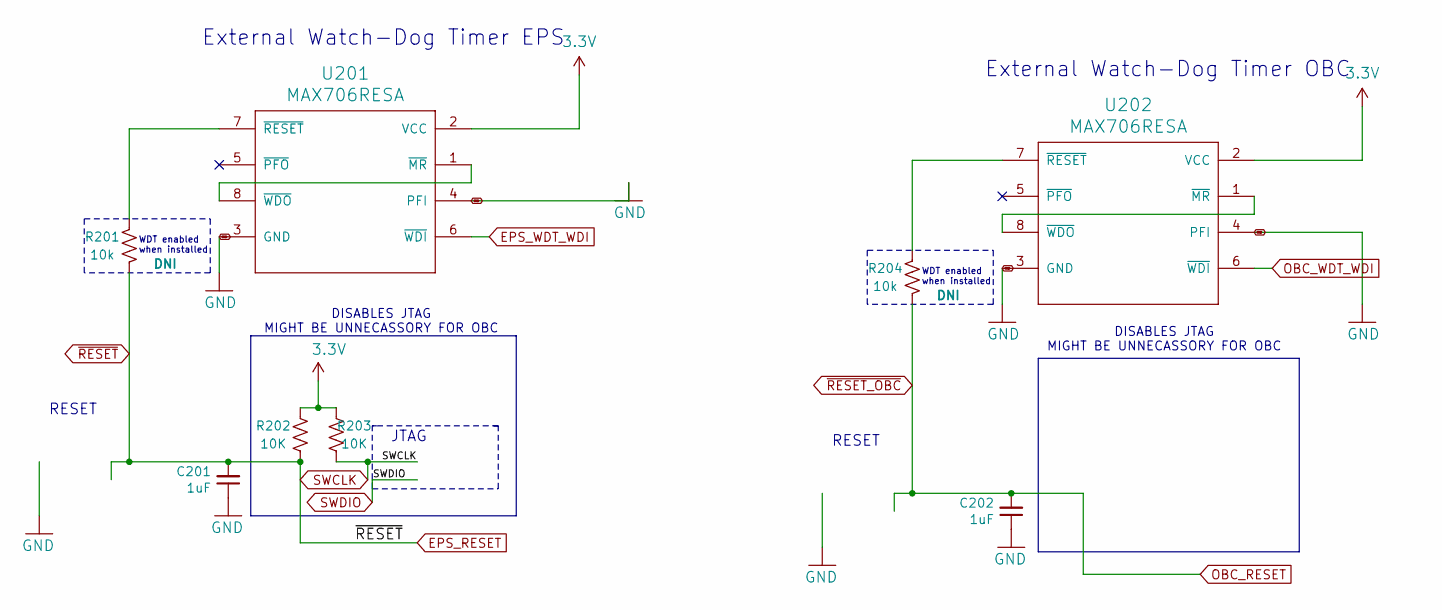
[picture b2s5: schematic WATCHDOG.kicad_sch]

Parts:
C201, C202: 1uF; C_0603_1608Metric
R201, R204: 10k; R_0603_1608Metric
R202, R203: 10K; R_0603_1608Metric
U201, U202: MAX706RESA; SO-8_3.9x4.9mm_P1.27mm; Manufacturer_Part_Number MAX706RESA

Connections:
3.3V: R202.1, R203.1, U201.2 (VCC), U202.2 (VCC); also elsewhere on the board
EPS_RESET: C201.2, R201.1, R202.2
EPS_WDT_WDI: U201.6 (~WDI)
GND: C201.1, C202.1, U201.3 (GND), U201.4 (PFI), U202.3 (GND), U202.4 (PFI); also elsewhere on the board
unnamed: U201.1 (~MR), U201.8 (~WDO)
unnamed: R201.2, U201.7 (~RESET)
unnamed: U202.1 (~MR), U202.8 (~WDO)
unnamed: R204.2, U202.7 (~RESET)
OBC_RESET: C202.2, R204.1; also elsewhere on the board
OBC_WDT_WDI: U202.6 (~WDI); also elsewhere on the board
SWCLK: R203.2; also elsewhere on the board

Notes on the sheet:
RESET
External Watch-Dog Timer EPS
DISABLES JTAG MIGHT BE UNNECASSORY FOR OBC
External Watch-Dog Timer OBC
JTAG
WDT enabled when installed
